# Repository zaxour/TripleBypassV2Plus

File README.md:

# Triple Bypass V2 Plus
My variant of Tian Feng's Triple Bypass V2, integrating pull up resistors and headphone restoration capability for Model 1 installs, as well as composite video restoration capability for all models.

All Genesis/Mega Drive revision instructions are linked below:

## Model 1 Installation Guides
[Model 1 - VA1-VA6](https://github.com/zaxour/TripleBypassV2Plus/blob/main/Documentation/3BP%20-%20M1VA0-VA6.pdf) 

[Model 1 - VA7](https://github.com/zaxour/TripleBypassV2Plus/blob/main/Documentation/3BP%20-%20M1VA7.pdf)
## Model 2 Installation Guides
[Model 2 - VA0-1.8](https://github.com/zaxour/TripleBypassV2Plus/blob/main/Documentation/3BP%20-%20M2VA0-1_8.pdf)

[Model 2 - VA2](https://github.com/zaxour/TripleBypassV2Plus/blob/main/Documentation/3BP%20-%20M2VA2.pdf)

[Model 2 - VA2.3](https://github.com/zaxour/TripleBypassV2Plus/blob/main/Documentation/3BP%20-%20M2VA2_3.pdf)

[Model 2 - VA3](https://github.com/zaxour/TripleBypassV2Plus/blob/main/Documentation/3BP%20-%20M2VA3.pdf)

[Model 2 - VA4](https://github.com/zaxour/TripleBypassV2Plus/blob/main/Documentation/3BP%20-%20M2VA4.pdf)

## Model 3 Installation Guides
[Model 3 - VA1](https://github.com/zaxour/TripleBypassV2Plus/blob/main/Documentation/3BP%20-%20M3VA1.pdf)

[Model 3 - VA2](https://github.com/zaxour/TripleBypassV2Plus/blob/main/Documentation/3BP%20-%20M3VA2.pdf)

## Sega CDX
[CDX](https://github.com/zaxour/TripleBypassV2Plus/blob/main/Documentation/3BP%20-%20CDX.pdf)

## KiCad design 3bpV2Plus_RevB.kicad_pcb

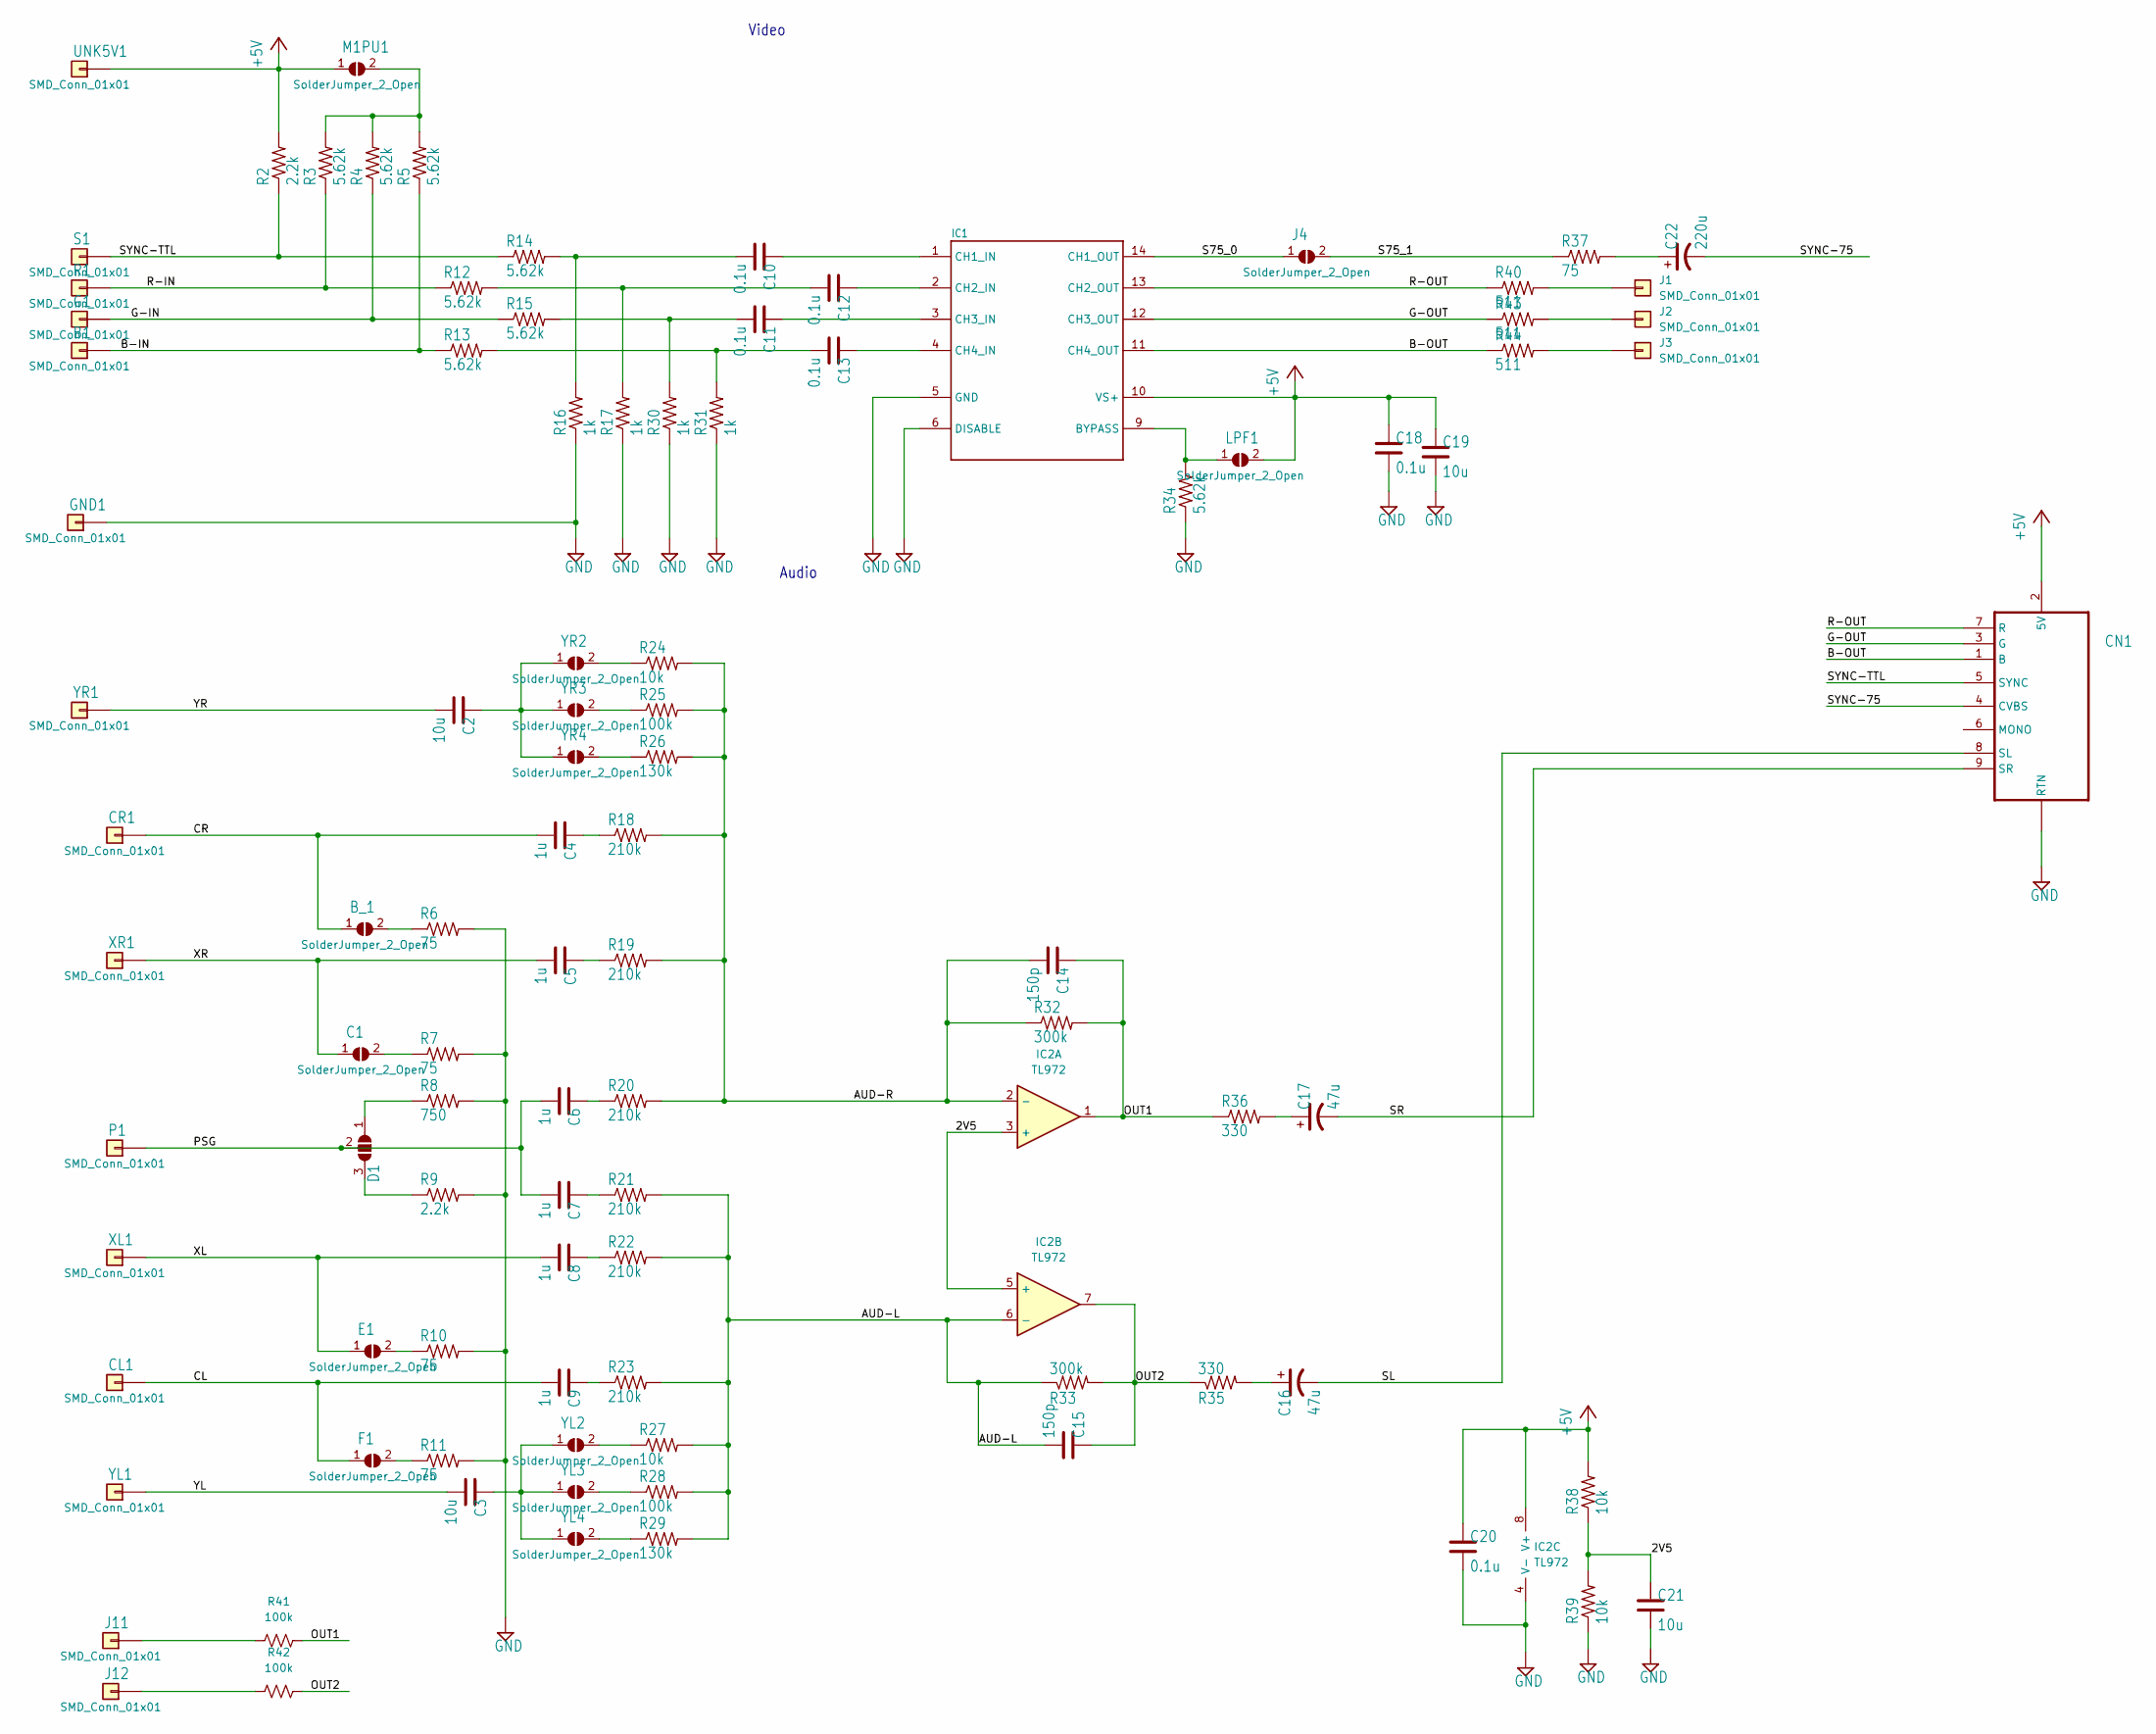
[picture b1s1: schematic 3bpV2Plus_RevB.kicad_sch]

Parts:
B1: SMD_Conn_01x01; SolderWirePad_1x01_SMD_1x2mm
B_1: SolderJumper_2_Open; SolderJumper-2
C1: SolderJumper_2_Open; SolderJumper-2
C2, C3: 10u; C_0805_2012Metric
C4, C5, C6, C7, C8, C9: 1u; C_0603_1608Metric
C10, C11, C12, C13, C18, C20: 0.1u; C_0603_1608Metric
C14, C15: 150p; C_0603_1608Metric
C16, C17: 47u; CP_EIA-3528-15_AVX-H
C19, C21: 10u; C_1206_3216Metric
C22: 220u; CP_EIA-3528-15_AVX-H
CL1: SMD_Conn_01x01; SolderWirePad_1x01_SMD_1x2mm
CN1: MD-90SM_MD2; MD90SM-MD2
CR1: SMD_Conn_01x01; SolderWirePad_1x01_SMD_1x2mm
D1: SolderJumper_3_Open; SolderJumper-3_P1.3mm_Open_RoundedPad1.0x1.5mm
E1: SolderJumper_2_Open; SolderJumper-2
F1: SolderJumper_2_Open; SolderJumper-2
G1: SMD_Conn_01x01; SolderWirePad_1x01_SMD_1x2mm
GND1: SMD_Conn_01x01; SolderWirePad_1x01_SMD_1x2mm
IC1: THS7374IPWR; TSSOP-14_4.4x5mm_P0.65mm
IC2: TL972; SOIC-8_3.9x4.9mm_P1.27mm
J1, J2, J3, J11, J12: SMD_Conn_01x01; SolderWirePad_1x01_SMD_1x2mm
J4: SolderJumper_2_Open; SolderJumper-2
LPF1: SolderJumper_2_Open; SolderJumper-2
M1PU1: SolderJumper_2_Open; SolderJumper-2
P1: SMD_Conn_01x01; SolderWirePad_1x01_SMD_1x2mm
R1: SMD_Conn_01x01; SolderWirePad_1x01_SMD_1x2mm
R2, R9: 2.2k; R_0603_1608Metric
R3, R4, R5, R12, R13, R14, R15, R34: 5.62k; R_0603_1608Metric
R6, R7, R10, R11, R37: 75; R_0603_1608Metric
R8: 750; R_0603_1608Metric
R16, R17, R30, R31: 1k; R_0603_1608Metric
R18, R19, R20, R21, R22, R23: 210k; R_0603_1608Metric
R24, R27, R38, R39: 10k; R_0603_1608Metric
R25, R28, R41, R42: 100k; R_0603_1608Metric
R26, R29: 130k; R_0603_1608Metric
R32, R33: 300k; R_0603_1608Metric
R35, R36: 330; R_0603_1608Metric
R40, R43, R44: 511; R_0603_1608Metric
S1: SMD_Conn_01x01; SolderWirePad_1x01_SMD_1x2mm
UNK5V1: SMD_Conn_01x01; SolderWirePad_1x01_SMD_1x2mm
XL1: SMD_Conn_01x01; SolderWirePad_1x01_SMD_1x2mm
XR1: SMD_Conn_01x01; SolderWirePad_1x01_SMD_1x2mm
YL1: SMD_Conn_01x01; SolderWirePad_1x01_SMD_1x2mm
YL2, YL3, YL4: SolderJumper_2_Open; SolderJumper-2
YR1: SMD_Conn_01x01; SolderWirePad_1x01_SMD_1x2mm
YR2, YR3, YR4: SolderJumper_2_Open; SolderJumper-2

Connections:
+5V: C18.1, C19.1, C20.1, CN1.2 (5V), IC1.10 (VS+), IC2.8 (V+), LPF1.2 (B), M1PU1.1 (A), R2.2, R38.2, UNK5V1.1
/2V5: C21.1, IC2.3 (+), IC2.5 (+), R38.1, R39.2
/AUD-L: C15.2, IC2.6 (-), R21.2, R22.2, R23.2, R27.2, R28.2, R29.2, R33.1
/AUD-R: C14.2, IC2.2 (-), R18.2, R19.2, R20.2, R24.2, R25.2, R26.2, R32.1
/B-IN: B1.1, R5.1, R13.1
/B-OUT: CN1.1 (B), IC1.11 (CH4_OUT), R44.1
/CL: C9.2, CL1.1, F1.1 (A)
/CR: B_1.1 (A), C4.2, CR1.1
/G-IN: G1.1, R4.1, R15.1
/G-OUT: CN1.3 (G), IC1.12 (CH3_OUT), R43.1
/OUT1: C14.1, IC2.1, R32.2, R36.1, R41.2
/OUT2: C15.1, IC2.7, R33.2, R35.1, R42.2
/PSG: C6.2, C7.2, D1.2 (C), P1.1
/R-IN: R1.1, R3.1, R12.1
/R-OUT: CN1.7 (R), IC1.13 (CH2_OUT), R40.1
/S75_0: IC1.14 (CH1_OUT), J4.1 (A)
/S75_1: J4.2 (B), R37.1
/SL: C16.2, CN1.8 (SL)
/SR: C17.2, CN1.9 (SR)
/SYNC-75: C22.2, CN1.4 (CVBS)
/SYNC-TTL: CN1.5 (SYNC), R2.1, R14.1, S1.1
/XL: C8.2, E1.1 (A), XL1.1
/XR: C1.1 (A), C5.2, XR1.1
/YL: C3.2, YL1.1
/YR: C2.2, YR1.1
GND: C18.2, C19.2, C20.2, C21.2, CN1.S1 (RTN), CN1.S2 (RTN), CN1.S3 (RTN), GND1.1, IC1.5 (GND), IC1.6 (DISABLE), IC2.4 (V-), R6.2, R7.2, R8.2, R9.2, R10.2, R11.2, R16.1, R17.1, R30.1, R31.1, R34.1, R39.1
unnamed: B_1.2 (B), R6.1
unnamed: C1.2 (B), R7.1
unnamed: C2.1, YR2.1 (A), YR3.1 (A), YR4.1 (A)
unnamed: C3.1, YL2.1 (A), YL3.1 (A), YL4.1 (A)
unnamed: C4.1, R18.1
unnamed: C5.1, R19.1
unnamed: C6.1, R20.1
unnamed: C7.1, R21.1
unnamed: C8.1, R22.1
unnamed: C9.1, R23.1
unnamed: C10.1, IC1.1 (CH1_IN)
unnamed: C10.2, R14.2, R16.2
unnamed: C11.1, IC1.3 (CH3_IN)
unnamed: C11.2, R15.2, R30.2
unnamed: C12.1, IC1.2 (CH2_IN)
unnamed: C12.2, R12.2, R17.2
unnamed: C13.1, IC1.4 (CH4_IN)
unnamed: C13.2, R13.2, R31.2
unnamed: C16.1, R35.2
unnamed: C17.1, R36.2
unnamed: C22.1, R37.2
unnamed: D1.1 (A), R8.1
unnamed: D1.3 (B), R9.1
unnamed: E1.2 (B), R10.1
unnamed: F1.2 (B), R11.1
unnamed: IC1.9 (BYPASS), LPF1.1 (A), R34.2
unnamed: J1.1, R40.2
unnamed: J2.1, R43.2
unnamed: J3.1, R44.2
unnamed: J11.1, R41.1
unnamed: J12.1, R42.1
unnamed: M1PU1.2 (B), R3.2, R4.2, R5.2
unnamed: R24.1, YR2.2 (B)
unnamed: R25.1, YR3.2 (B)
unnamed: R26.1, YR4.2 (B)
unnamed: R27.1, YL2.2 (B)
unnamed: R28.1, YL3.2 (B)
unnamed: R29.1, YL4.2 (B)

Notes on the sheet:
Video
Audio

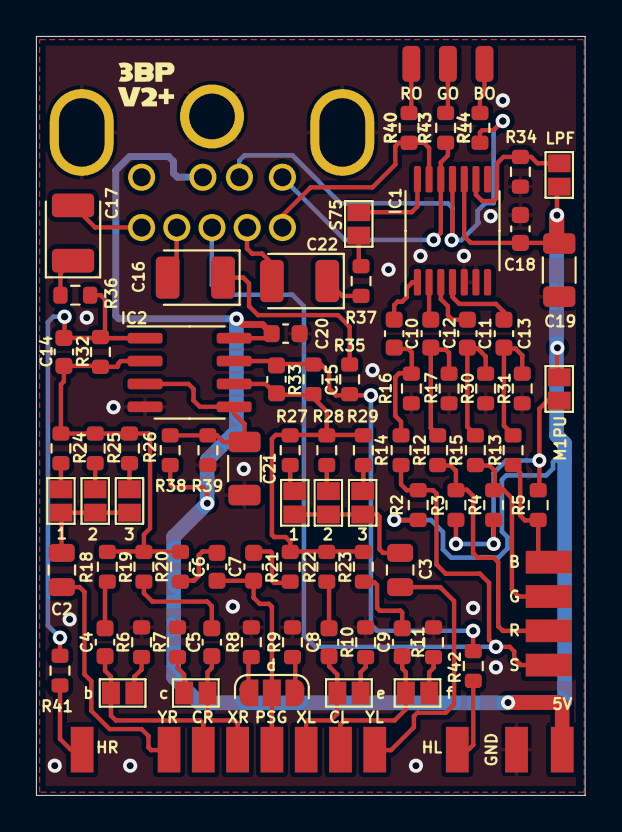
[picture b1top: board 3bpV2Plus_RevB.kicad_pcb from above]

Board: 2 copper layers, 30.5 x 42.2 mm, 99 parts (1 on the bottom side), 64 nets.

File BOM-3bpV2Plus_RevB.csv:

Comment,Designator,Footprint,LCSC
220u,C22,CP_EIA-3528-15_AVX-H,C122252
10u,"C19,C21",C_1206_3216Metric,C13585
0.1u,"C10,C11,C12,C13,C18,C20",C_0603_1608Metric,C14663
1u,"C4,C5,C6,C7,C8,C9",C_0603_1608Metric,C15849
10u,"C2,C3",C_0805_2012Metric,C15850
1k,"R17,R30,R31",R_0603_1608Metric,C21190
130k,"R26,R29",R_0603_1608Metric,C22795
210k,"R18,R19,R20,R21,R22,R23",R_0603_1608Metric,C22952
300k,"R32,R33",R_0603_1608Metric,C23024
330,"R35,R36",R_0603_1608Metric,C23138
5.62k,"R12,R13,R14,R15,R3,R34,R4,R5",R_0603_1608Metric,C23188
750,R8,R_0603_1608Metric,C23241
100k,"R25,R28,R41,R42",R_0603_1608Metric,C25803
10k,"R24,R27,R38,R39",R_0603_1608Metric,C25804
THS7374IPWR,IC1,TSSOP-14_4.4x5mm_P0.65mm,C2652746
150p,"C14,C15",C_0603_1608Metric,C37298
2.2k,"R2,R9",R_0603_1608Metric,C4190
75,"R10,R11,R6,R7",R_0603_1608Metric,C4275
TL972,IC2,SOIC-8_3.9x4.9mm_P1.27mm,C46127
47u,"C16,C17",CP_EIA-3528-15_AVX-H,C7207
MD-90SM_MD2,CN1,MD90SM-MD2,
SolderJumper_3_Open,D1,SolderJumper-3_P1.3mm_Open_RoundedPad1.0x1.5mm,
SolderJumper_2_Open,YR4,SolderJumper-2,
SolderJumper_2_Open,YR3,SolderJumper-2,
SolderJumper_2_Open,YR2,SolderJumper-2,
SolderJumper_2_Open,YL4,SolderJumper-2,
SolderJumper_2_Open,YL3,SolderJumper-2,
SolderJumper_2_Open,YL2,SolderJumper-2,
SolderJumper_2_Open,M1PU1,SolderJumper-2,
SolderJumper_2_Open,LPF1,SolderJumper-2,
SolderJumper_2_Open,F1,SolderJumper-2,
SolderJumper_2_Open,E1,SolderJumper-2,
SolderJumper_2_Open,C1,SolderJumper-2,
SolderJumper_2_Open,B_1,SolderJumper-2,
75,R37,R_0603_1608Metric,
1k,R16,R_0603_1608Metric,
SolderJumper_2_Open,J4,SolderJumper-2,
511,R43,R_0603_1608Metric,
511,R44,R_0603_1608Metric,
511,R40,R_0603_1608Metric,

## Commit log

2023-12-10 Add files via upload
    Updated M1VA7 instructions with corrections
2024-02-18 Add files via upload
    Corrected capacitor removal instructions for M1VA3
2025-02-02 Add files via upload
    Corrected errors (XL and XR swapped, need to remove CE10) on Model 3 VA1 installation procedure (Thanks Voultar)
    Corrected XL incorrect solder point - Thanks Duncan1111
2025-04-20 Add files via upload
    Corrected YR resistor removal and XL/XR solder points

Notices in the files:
3bpV2Plus_RevB.kicad_pcb:
CERN OHL v1.2
Licensed under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
